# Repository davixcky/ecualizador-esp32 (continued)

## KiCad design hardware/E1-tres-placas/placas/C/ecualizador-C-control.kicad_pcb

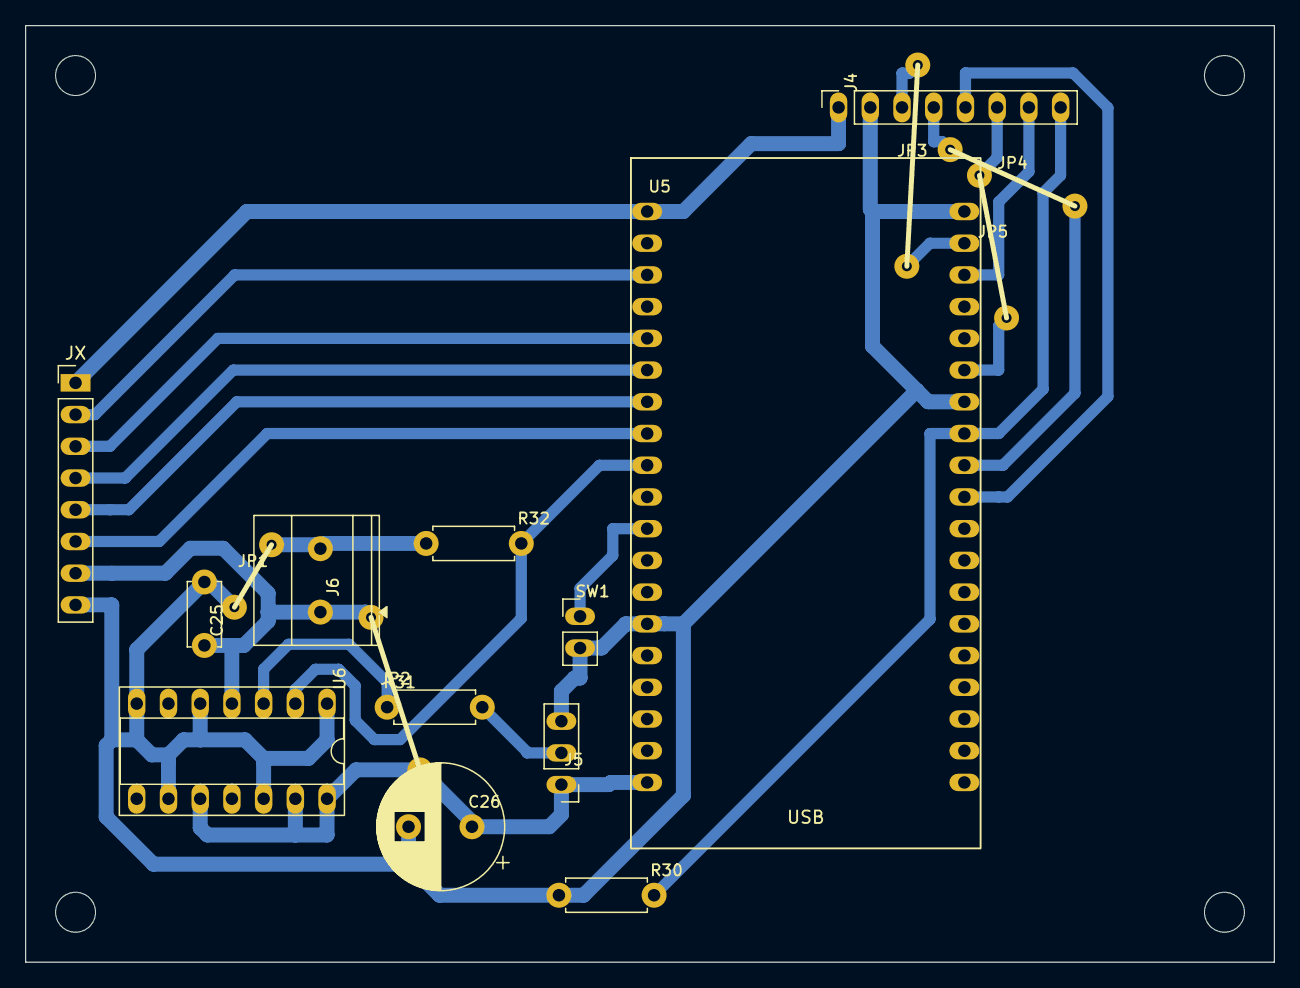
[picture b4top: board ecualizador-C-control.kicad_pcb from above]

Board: 2 copper layers, 100.0 x 75.0 mm, 21 parts (0 on the bottom side), 18 nets.

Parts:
C25: 100n; UnaCara_C25
C26: 1000u 10V; UnaCara_C26
H1, H2, H3, H4: MountingHole_3.2mm_M3
J4: Waveshare 1.9 ST7789V2; UnaCara_J4
J5: NeoPixel 5V DIN GND; UnaCara_J5
J6: Entrada 5V 3A; UnaCara_J6
JP1, JP2, JP3, JP4, JP5: puente; Puente_alambre
JX: Conector entre placas; PinHeader_1x08_P2.54mm_Vertical
R30: 10k; UnaCara_R30
R31: 330; UnaCara_R31
R32: 10k; UnaCara_R32
SW1: Pulsador; UnaCara_SW1
U5: ESP32-DevKitC V4; UnaCara_U5
U6: 74AHCT125; UnaCara_U6

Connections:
+3V3: J4.1, JX.1, U5.1
+5V: C25.1, C26.1, J5.1, J6.1, JP2.1, JX.7, U5.19, U6.4, U6.10, U6.13, U6.14
/ADC_A: JX.5, U5.7
/ADC_FFT: JX.6, U5.8
/ADC_G: JX.3, U5.5
/ADC_M: JX.4, U5.6
/BTN: SW1.1, U5.11
/LED_5V: R31.1, U6.3
/LED_DATA: R32.1, U5.9, U6.2
/LED_DIN: J5.2, R31.2
/TFT_BL: J4.8, R30.1, U5.27
/TFT_CS: J4.5, U5.29
/TFT_DC: J4.6, JP5.1, U5.25
/TFT_MOSI: J4.3, JP3.1, U5.21
/TFT_RST: J4.7, U5.22
/TFT_SCK: J4.4, JP4.1, U5.28
/VREF: JX.2, U5.3
GND: C25.2, C26.2, J4.2, J5.3, J6.2, JP1.1, JX.8, R30.2, R32.2, SW1.2, U5.14, U5.20, U5.26, U6.1, U6.5, U6.7, U6.9, U6.12

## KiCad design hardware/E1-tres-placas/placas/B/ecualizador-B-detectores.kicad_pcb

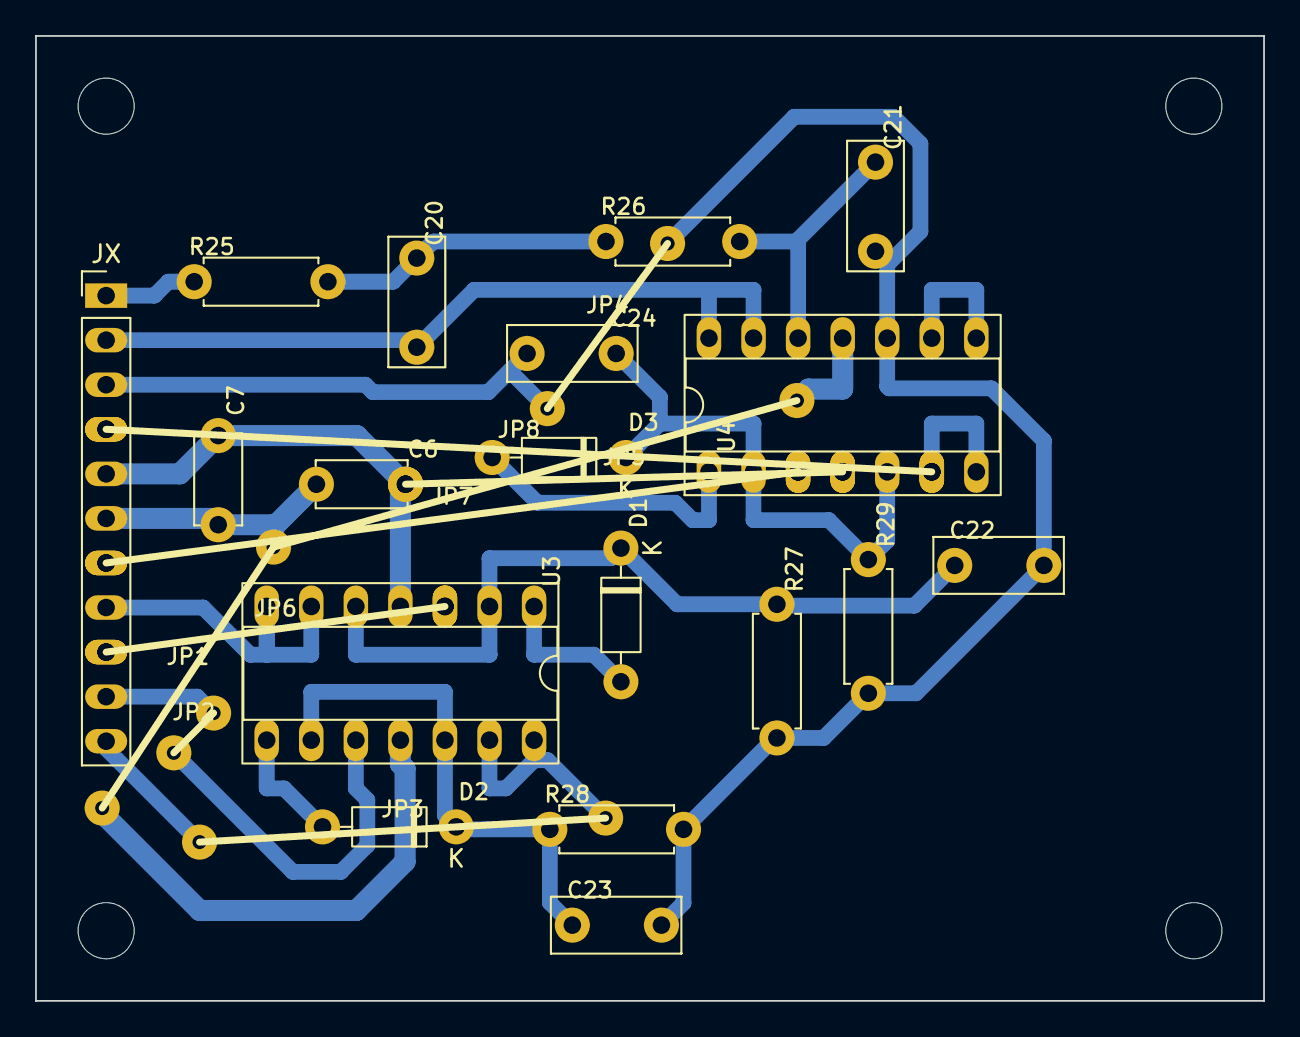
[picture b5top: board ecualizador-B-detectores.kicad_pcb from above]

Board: 2 copper layers, 70.0 x 55.0 mm, 30 parts (0 on the bottom side), 20 nets.

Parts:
C6: 100n; UnaCara_C6
C7: 100n; UnaCara_C7
C20: 4n7 film; UnaCara_C20
C21: 2n2 film; UnaCara_C21
C22: 100n film; UnaCara_C22
C23: 100n film; UnaCara_C23
C24: 100n film; UnaCara_C24
D1: 1N4148; UnaCara_D1
D2: 1N4148; UnaCara_D2
D3: 1N4148; UnaCara_D3
H1, H2, H3, H4: MountingHole_3.2mm_M3
JP1, JP2, JP3, JP4, JP5, JP6, JP7, JP8: puente; Puente_alambre
JX: Conector entre placas; PinHeader_1x11_P2.54mm_Vertical
R25: 10k 1%; UnaCara_R25
R26: 10k 1%; UnaCara_R26
R27: 220k; UnaCara_R27
R28: 220k; UnaCara_R28
R29: 220k; UnaCara_R29
U3: MCP6004; UnaCara_U3
U4: MCP6004; UnaCara_U4

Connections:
+3.3VA: C6.1, C7.1, JP5.1, JX.5, U3.4, U4.4
/ADC_A: JP8.1, JX.4, U4.6, U4.7
/ADC_FFT: C20.2, JX.2, U4.13, U4.14
/ADC_G: JX.8, U3.6, U3.7
/ADC_M: JP3.1, JX.11, U3.13, U3.14
/A_W: JP7.1, JX.7, U4.3
/EQ_OUT: JX.1, R25.1
/G_W: JP6.1, JX.9, U3.3
/M_W: JP2.1, JX.10, U3.10
/VREF: C21.2, C22.2, C23.2, C24.2, JP4.1, JX.3, R27.2, R28.2, R29.2, U4.10
GND: C6.2, C7.2, JP1.1, JX.6, U3.11, U4.11
unnamed: C20.1, R25.2, R26.1
unnamed: D1.2, U3.1
unnamed: C22.1, D1.1, R27.1, U3.2, U3.5
unnamed: D2.2, U3.8
unnamed: C23.1, D2.1, R28.1, U3.9, U3.12
unnamed: D3.2, U4.1
unnamed: C24.1, D3.1, R29.1, U4.2, U4.5
unnamed: C21.1, R26.2, U4.12
unnamed: U4.8, U4.9

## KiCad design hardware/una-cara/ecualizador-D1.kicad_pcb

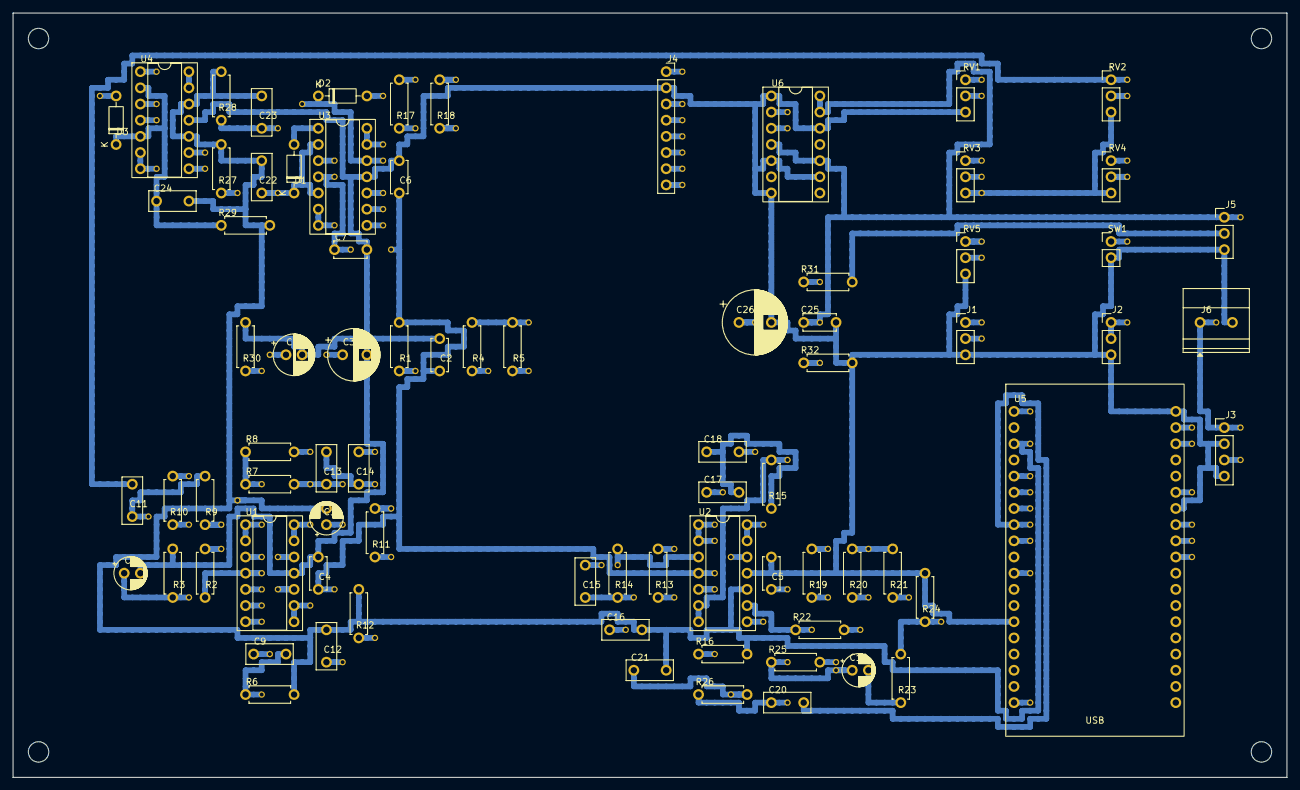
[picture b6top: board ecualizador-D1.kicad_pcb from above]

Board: 2 copper layers, 200.0 x 120.0 mm, 163 parts (0 on the bottom side), 59 nets.

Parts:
C1: 100u 10V; UnaCara_C1
C2: 100n; UnaCara_C2
C3: 470u 10V; UnaCara_C3
C4: 100n; UnaCara_C4
C5: 100n; UnaCara_C5
C6: 100n; UnaCara_C6
C7: 100n; UnaCara_C7
C8: 10u 16V; UnaCara_C8
C9: 1u film; UnaCara_C9
C10: 10u 16V; UnaCara_C10
C11: 100n film; UnaCara_C11
C12: 47n film; UnaCara_C12
C13: 10n film; UnaCara_C13
C14: 10n film; UnaCara_C14
C15: 10n film; UnaCara_C15
C16: 4n7 film; UnaCara_C16
C17: 10n film; UnaCara_C17
C18: 10n film; UnaCara_C18
C19: 10u 16V; UnaCara_C19
C20: 4n7 film; UnaCara_C20
C21: 2n2 film; UnaCara_C21
C22: 100n film; UnaCara_C22
C23: 100n film; UnaCara_C23
C24: 100n film; UnaCara_C24
C25: 100n; UnaCara_C25
C26: 1000u 10V; UnaCara_C26
D1: 1N4148; UnaCara_D1
D2: 1N4148; UnaCara_D2
D3: 1N4148; UnaCara_D3
H1, H2, H3, H4: MountingHole_3.2mm_M3
J1: Entrada de línea 3,5 mm; UnaCara_J1
J2: Salida de línea 3,5 mm; UnaCara_J2
J3: PAM8403; UnaCara_J3
J4: Waveshare 1.9 ST7789V2; UnaCara_J4
J5: NeoPixel 5V DIN GND; UnaCara_J5
J6: Entrada 5V 3A; UnaCara_J6
R1: 10; UnaCara_R1
R2: 10k 1%; UnaCara_R2
R3: 10k 1%; UnaCara_R3
R4: 10k; UnaCara_R4
R5: 10k; UnaCara_R5
R6: 100k; UnaCara_R6
R7: 22k 1%; UnaCara_R7
R8: 10k 1%; UnaCara_R8
R9: 10k 1%; UnaCara_R9
R10: 10k 1%; UnaCara_R10
R11: 27k 1%; UnaCara_R11
R12: 56k 1%; UnaCara_R12
R13: 10k 1%; UnaCara_R13
R14: 10k 1%; UnaCara_R14
R15: 2k7 1%; UnaCara_R15
R16: 5k6 1%; UnaCara_R16
R17: 47k 1%; UnaCara_R17
R18: 47k 1%; UnaCara_R18
R19: 47k 1%; UnaCara_R19
R20: 47k 1%; UnaCara_R20
R21: 47k 1%; UnaCara_R21
R22: 100k 1%; UnaCara_R22
R23: 100; UnaCara_R23
R24: 47k; UnaCara_R24
R25: 10k 1%; UnaCara_R25
R26: 10k 1%; UnaCara_R26
R27: 220k; UnaCara_R27
R28: 220k; UnaCara_R28
R29: 220k; UnaCara_R29
R30: 10k; UnaCara_R30
R31: 330; UnaCara_R31
R32: 10k; UnaCara_R32
RV1: 10k log; UnaCara_RV1
RV2: 10k lin; UnaCara_RV2
RV3: 10k lin; UnaCara_RV3
RV4: 10k lin; UnaCara_RV4
RV5: 10k log; UnaCara_RV5
SW1: Pulsador; UnaCara_SW1
U1: MCP6004; UnaCara_U1
U2: MCP6004; UnaCara_U2
U3: MCP6004; UnaCara_U3
U4: MCP6004; UnaCara_U4
U5: ESP32-DevKitC V4; UnaCara_U5
U6: 74AHCT125; UnaCara_U6
W1, W2: Cable aislado /VREF
W3, W4, W5, W6, W7: Cable aislado +3.3VA
W8, W9, W10, W11: Cable aislado +5V
W12, W13: Cable aislado /LINEA
W14, W15, W16: Cable aislado /PRE
W17: Cable aislado Net-(D1-K)
W18, W19: Cable aislado Net-(D2-K)
W20, W21: Cable aislado Net-(U2C--)
W22: Cable aislado /ADC_FFT
W23: Cable aislado /AGUDOS
W24, W25: Cable aislado /EQ_OUT
W26: Cable aislado /GRAVES
W27, W28: Cable aislado /MEDIOS
W29, W30: Cable aislado /MED_HP
W31, W32: Cable aislado Net-(U1A-+)
W33, W34: Cable aislado +3V3
W35: Cable aislado /ADC_A
W36: Cable aislado /ADC_G
W37: Cable aislado /ADC_M
W38, W39: Cable aislado /A_W
W40, W41: Cable aislado /G_W
W42, W43: Cable aislado /LED_DATA
W44, W45: Cable aislado /M_INV
W46, W47: Cable aislado /M_W
W48, W49: Cable aislado /TFT_BL
W50: Cable aislado Net-(C11-Pad1)
W51: Cable aislado Net-(C13-Pad2)
W52: Cable aislado Net-(C15-Pad1)
W53: Cable aislado Net-(C20-Pad1)
W54: Cable aislado Net-(R4-Pad2)
W55: Cable aislado Net-(U1B-+)
W56: Cable aislado Net-(U1B--)
W57, W58: Cable aislado Net-(U1C-+)
W59, W60: Cable aislado Net-(U1D-+)
W61: Cable aislado Net-(U2A-+)
W62, W63: Cable aislado Net-(U2B-+)
W64: Cable aislado Net-(U2D-+)
W65, W66: Cable aislado Net-(U4C--)
W67: Cable aislado /AMP_IN
W68: Cable aislado /BTN
W69: Cable aislado /IN_L
W70: Cable aislado /IN_R
W71: Cable aislado /LED_5V
W72: Cable aislado /TFT_CS
W73: Cable aislado /TFT_DC
W74: Cable aislado /TFT_MOSI
W75: Cable aislado /TFT_RST
W76: Cable aislado /TFT_SCK
W77: Cable aislado Net-(C10-Pad1)
W78: Cable aislado Net-(C9-Pad1)
W79: Cable aislado Net-(D2-A)
W80: Cable aislado Net-(D3-A)

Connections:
+3.3VA: C1.1, C2.1, C4.1, C5.1, C6.1, C7.1, R1.2, R2.1, U1.4, U2.4, U3.4, U4.4, W3.1, W3.2, W4.1, W4.2, W5.1, W5.2, W6.1, W6.2, W7.1, W7.2
+3V3: J4.1, R1.1, U5.1, W33.1, W33.2, W34.1, W34.2
+5V: C3.1, C25.1, C26.1, J3.1, J5.1, J6.1, U5.19, U6.4, U6.10, U6.13, U6.14, W8.1, W8.2, W9.1, W9.2, W10.1, W10.2, W11.1, W11.2
/ADC_A: U4.6, U4.7, U5.7, W35.1, W35.2
/ADC_FFT: C20.2, U2.13, U2.14, U5.8, W22.1, W22.2
/ADC_G: U3.6, U3.7, U5.5, W36.1, W36.2
/ADC_M: U3.13, U3.14, U5.6, W37.1, W37.2
/AGUDOS: R15.2, RV4.1, U2.6, U2.7, W23.1, W23.2
/AMP_IN: J3.3, RV5.2, W67.1, W67.2
/A_W: R21.1, RV4.2, U4.3, W38.1, W38.2, W39.1, W39.2
/BTN: SW1.1, U5.11, W68.1, W68.2
/EQ_OUT: C19.1, R22.2, R25.1, U2.8, W24.1, W24.2, W25.1, W25.2
/GRAVES: C11.2, RV2.1, U1.8, U1.9, W26.1, W26.2
/G_W: R19.1, RV2.2, U3.3, W40.1, W40.2, W41.1, W41.2
/IN_L: J1.T, R4.1, W69.1, W69.2
/IN_R: J1.R, R5.1, W70.1, W70.2
/LED_5V: R31.1, U6.3, W71.1, W71.2
/LED_DATA: R32.1, U5.9, U6.2, W42.1, W42.2, W43.1, W43.2
/LED_DIN: J5.2, R31.2
/LINEA: J2.R, J2.T, R23.2, R24.1, RV5.1, W12.1, W12.2, W13.1, W13.2
/MEDIOS: C15.2, RV3.1, U2.1, U2.2, W27.1, W27.2, W28.1, W28.2
/MED_HP: R11.2, R13.1, U1.13, U1.14, W29.1, W29.2, W30.1, W30.2
/M_INV: R18.2, R20.1, U4.8, W44.1, W44.2, W45.1, W45.2
/M_W: R17.1, RV3.2, U3.10, W46.1, W46.2, W47.1, W47.2
/PRE: C13.1, C17.1, R7.2, R9.1, U1.7, W14.1, W14.2, W15.1, W15.2, W16.1, W16.2
/TFT_BL: J4.8, R30.1, U5.27, W48.1, W48.2, W49.1, W49.2
/TFT_CS: J4.5, U5.29, W72.1, W72.2
/TFT_DC: J4.6, U5.25, W73.1, W73.2
/TFT_MOSI: J4.3, U5.21, W74.1, W74.2
/TFT_RST: J4.7, U5.22, W75.1, W75.2
/TFT_SCK: J4.4, U5.28, W76.1, W76.2
/VREF: C10.2, C12.2, C16.2, C21.2, C22.2, C23.2, C24.2, R6.2, R12.2, R16.2, R27.2, R28.2, R29.2, RV2.3, RV3.3, RV4.3, U1.1, U1.2, U2.10, U4.10, U4.12, U5.3, W1.1, W1.2, W2.1, W2.2
GND: C1.2, C2.2, C3.2, C4.2, C5.2, C6.2, C7.2, C8.2, C25.2, C26.2, J1.S, J2.S, J3.2, J3.4, J4.2, J5.3, J6.2, R3.2, R24.2, R30.2, R32.2, RV1.3, RV5.3, SW1.2, U1.11, U2.11, U3.11, U4.11, U5.14, U5.20, U5.26, U6.1, U6.5, U6.7, U6.9, U6.12
unnamed: C9.1, RV1.2, W78.1, W78.2
unnamed: C10.1, R8.2, W77.1, W77.2
unnamed: C11.1, R9.2, R10.1, W50.1, W50.2
unnamed: C13.2, C14.1, R11.1, W51.1, W51.2
unnamed: C15.1, R13.2, R14.1, W52.1, W52.2
unnamed: C17.2, C18.1, R15.1
unnamed: C19.2, R23.1
unnamed: C20.1, R25.2, R26.1, W53.1, W53.2
unnamed: D1.2, U3.1
unnamed: C22.1, D1.1, R27.1, U3.2, U3.5, W17.1, W17.2
unnamed: D2.2, U3.8, W79.1, W79.2
unnamed: C23.1, D2.1, R28.1, U3.9, U3.12, W18.1, W18.2, W19.1, W19.2
unnamed: D3.2, U4.1, W80.1, W80.2
unnamed: C24.1, D3.1, R29.1, U4.2, U4.5
unnamed: R4.2, R5.2, RV1.1, W54.1, W54.2
unnamed: C8.1, R2.2, R3.1, U1.3, W31.1, W31.2, W32.1, W32.2
unnamed: C9.2, R6.1, U1.5, W55.1, W55.2
unnamed: R7.1, R8.1, U1.6, W56.1, W56.2
unnamed: C12.1, R10.2, U1.10, W57.1, W57.2, W58.1, W58.2
unnamed: C14.2, R12.1, U1.12, W59.1, W59.2, W60.1, W60.2
unnamed: C16.1, R14.2, U2.3, W61.1, W61.2
unnamed: C18.2, R16.1, U2.5, W62.1, W62.2, W63.1, W63.2
unnamed: R19.2, R20.2, R21.2, R22.1, U2.9, W20.1, W20.2, W21.1, W21.2
unnamed: C21.1, R26.2, U2.12, W64.1, W64.2
unnamed: R17.2, R18.1, U4.9, W65.1, W65.2, W66.1, W66.2
unnamed: U4.13, U4.14

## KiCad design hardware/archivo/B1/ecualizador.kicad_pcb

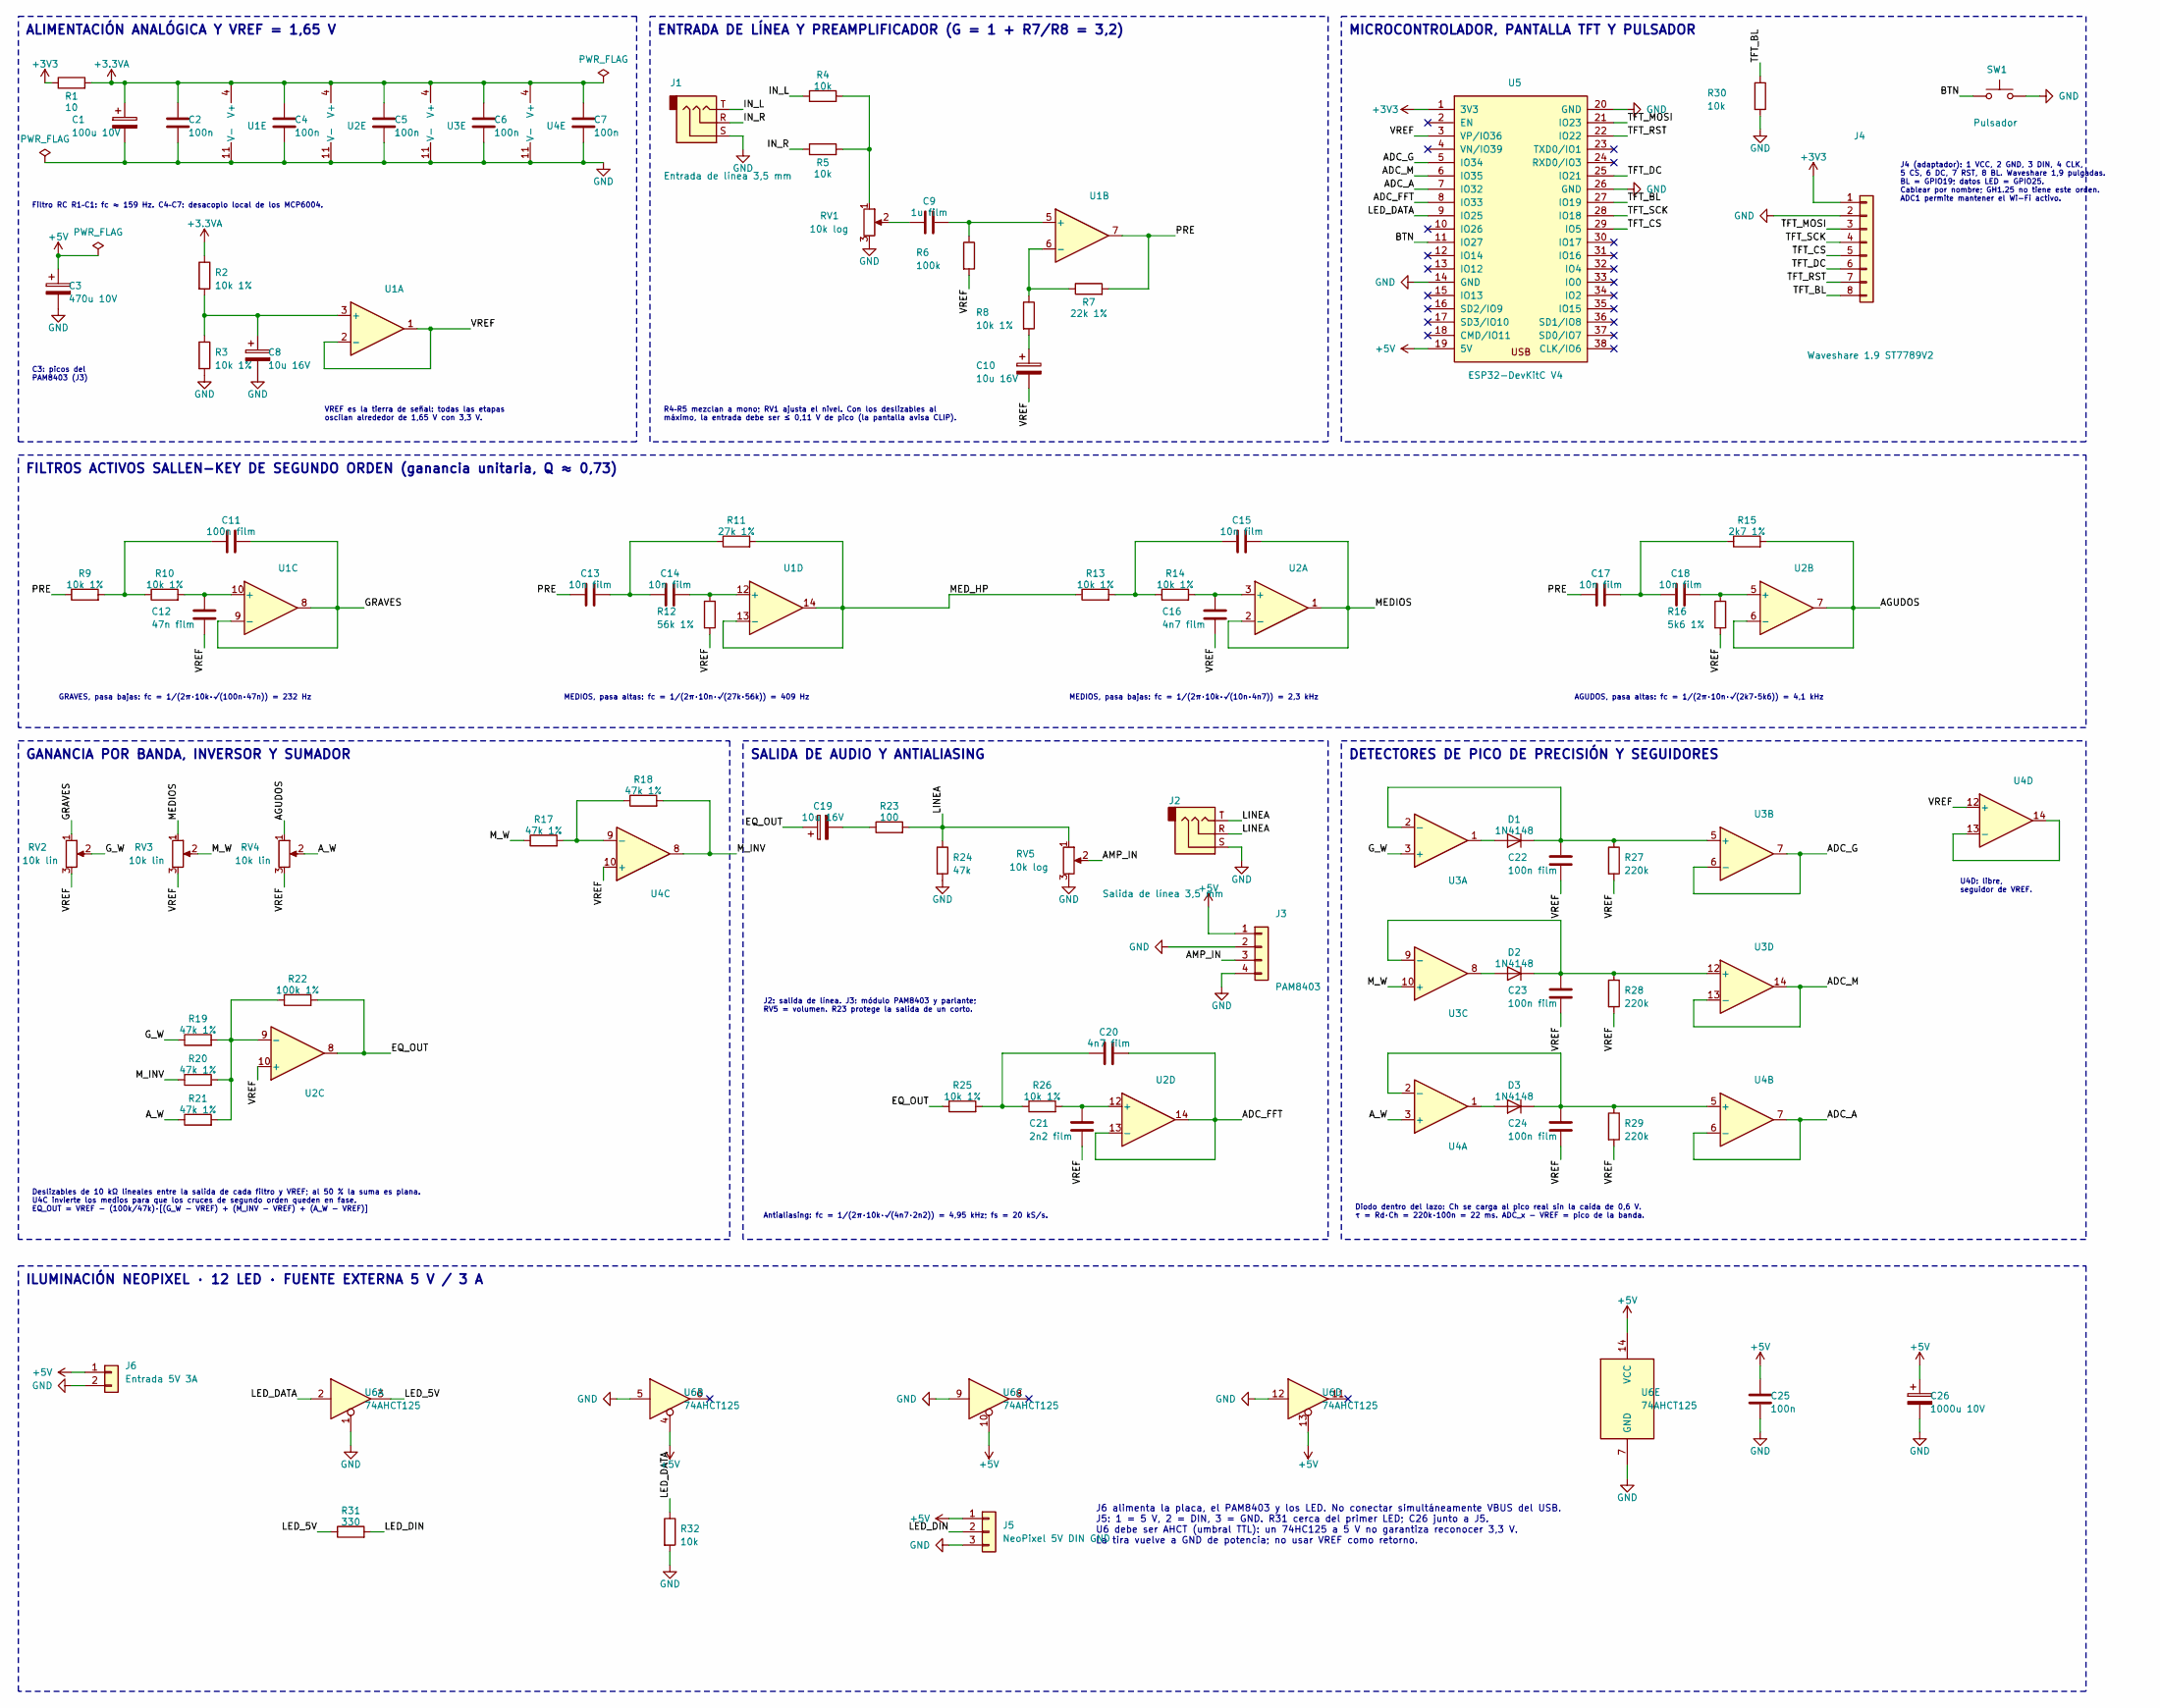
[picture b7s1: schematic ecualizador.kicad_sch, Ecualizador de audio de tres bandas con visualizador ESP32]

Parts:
C1: 100u 10V; UnaCara_C1
C2: 100n; UnaCara_C2
C3: 470u 10V; UnaCara_C3
C4: 100n; UnaCara_C4
C5: 100n; UnaCara_C5
C6: 100n; UnaCara_C6
C7: 100n; UnaCara_C7
C8: 10u 16V; UnaCara_C8
C9: 1u film; UnaCara_C9
C10: 10u 16V; UnaCara_C10
C11: 100n film; UnaCara_C11
C12: 47n film; UnaCara_C12
C13: 10n film; UnaCara_C13
C14: 10n film; UnaCara_C14
C15: 10n film; UnaCara_C15
C16: 4n7 film; UnaCara_C16
C17: 10n film; UnaCara_C17
C18: 10n film; UnaCara_C18
C19: 10u 16V; UnaCara_C19
C20: 4n7 film; UnaCara_C20
C21: 2n2 film; UnaCara_C21
C22: 100n film; UnaCara_C22
C23: 100n film; UnaCara_C23
C24: 100n film; UnaCara_C24
C25: 100n; UnaCara_C25
C26: 1000u 10V; UnaCara_C26
D1: 1N4148; UnaCara_D1
D2: 1N4148; UnaCara_D2
D3: 1N4148; UnaCara_D3
J1: Entrada de línea 3,5 mm; UnaCara_J1
J2: Salida de línea 3,5 mm; UnaCara_J2
J3: PAM8403; UnaCara_J3
J4: Waveshare 1.9 ST7789V2; UnaCara_J4
J5: NeoPixel 5V DIN GND; UnaCara_J5
J6: Entrada 5V 3A; UnaCara_J6
R1: 10; UnaCara_R1
R2: 10k 1%; UnaCara_R2
R3: 10k 1%; UnaCara_R3
R4: 10k; UnaCara_R4
R5: 10k; UnaCara_R5
R6: 100k; UnaCara_R6
R7: 22k 1%; UnaCara_R7
R8: 10k 1%; UnaCara_R8
R9: 10k 1%; UnaCara_R9
R10: 10k 1%; UnaCara_R10
R11: 27k 1%; UnaCara_R11
R12: 56k 1%; UnaCara_R12
R13: 10k 1%; UnaCara_R13
R14: 10k 1%; UnaCara_R14
R15: 2k7 1%; UnaCara_R15
R16: 5k6 1%; UnaCara_R16
R17: 47k 1%; UnaCara_R17
R18: 47k 1%; UnaCara_R18
R19: 47k 1%; UnaCara_R19
R20: 47k 1%; UnaCara_R20
R21: 47k 1%; UnaCara_R21
R22: 100k 1%; UnaCara_R22
R23: 100; UnaCara_R23
R24: 47k; UnaCara_R24
R25: 10k 1%; UnaCara_R25
R26: 10k 1%; UnaCara_R26
R27: 220k; UnaCara_R27
R28: 220k; UnaCara_R28
R29: 220k; UnaCara_R29
R30: 10k; UnaCara_R30
R31: 330; UnaCara_R31
R32: 10k; UnaCara_R32
RV1: 10k log; UnaCara_RV1
RV2: 10k lin; UnaCara_RV2
RV3: 10k lin; UnaCara_RV3
RV4: 10k lin; UnaCara_RV4
RV5: 10k log; UnaCara_RV5
SW1: Pulsador; UnaCara_SW1
U1: MCP6004; UnaCara_U1
U2: MCP6004; UnaCara_U2
U3: MCP6004; UnaCara_U3
U4: MCP6004; UnaCara_U4
U5: ESP32-DevKitC V4; UnaCara_U5
U6: 74AHCT125; UnaCara_U6

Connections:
+3.3VA: C1.1, C2.1, C4.1, C5.1, C6.1, C7.1, R1.2, R2.1, U1.4 (V+), U2.4 (V+), U3.4 (V+), U4.4 (V+)
+3V3: J4.1, R1.1, U5.1 (3V3)
+5V: C3.1, C25.1, C26.1, J3.1, J5.1, J6.1, U5.19 (5V), U6.4, U6.10, U6.13, U6.14 (VCC)
/ADC_A: U4.6 (-), U4.7, U5.7 (IO32)
/ADC_FFT: C20.2, U2.13 (-), U2.14, U5.8 (IO33)
/ADC_G: U3.6 (-), U3.7, U5.5 (IO34)
/ADC_M: U3.13 (-), U3.14, U5.6 (IO35)
/AGUDOS: R15.2, RV4.1, U2.6 (-), U2.7
/AMP_IN: J3.3, RV5.2
/A_W: R21.1, RV4.2, U4.3 (+)
/BTN: SW1.1, U5.11 (IO27)
/EQ_OUT: C19.1, R22.2, R25.1, U2.8
/GRAVES: C11.2, RV2.1, U1.8, U1.9 (-)
/G_W: R19.1, RV2.2, U3.3 (+)
/IN_L: J1.T, R4.1
/IN_R: J1.R, R5.1
/LED_5V: R31.1, U6.3
/LED_DATA: R32.1, U5.9 (IO25), U6.2
/LED_DIN: J5.2, R31.2
/LINEA: J2.R, J2.T, R23.2, R24.1, RV5.1
/MEDIOS: C15.2, RV3.1, U2.1, U2.2 (-)
/MED_HP: R11.2, R13.1, U1.13 (-), U1.14
/M_INV: R18.2, R20.1, U4.8
/M_W: R17.1, RV3.2, U3.10 (+)
/PRE: C13.1, C17.1, R7.2, R9.1, U1.7
/TFT_BL: J4.8, R30.1, U5.27 (IO19)
/TFT_CS: J4.5, U5.29 (IO5)
/TFT_DC: J4.6, U5.25 (IO21)
/TFT_MOSI: J4.3, U5.21 (IO23)
/TFT_RST: J4.7, U5.22 (IO22)
/TFT_SCK: J4.4, U5.28 (IO18)
/VREF: C10.2, C12.2, C16.2, C21.2, C22.2, C23.2, C24.2, R6.2, R12.2, R16.2, R27.2, R28.2, R29.2, RV2.3, RV3.3, RV4.3, U1.1, U1.2 (-), U2.10 (+), U4.10 (+), U4.12 (+), U5.3 (VP/IO36)
GND: C1.2, C2.2, C3.2, C4.2, C5.2, C6.2, C7.2, C8.2, C25.2, C26.2, J1.S, J2.S, J3.2, J3.4, J4.2, J5.3, J6.2, R3.2, R24.2, R30.2, R32.2, RV1.3, RV5.3, SW1.2, U1.11 (V-), U2.11 (V-), U3.11 (V-), U4.11 (V-), U5.14 (GND), U5.20 (GND), U5.26 (GND), U6.1, U6.5, U6.7 (GND), U6.9, U6.12
unnamed: C9.1, RV1.2
unnamed: C10.1, R8.2
unnamed: C11.1, R9.2, R10.1
unnamed: C13.2, C14.1, R11.1
unnamed: C15.1, R13.2, R14.1
unnamed: C17.2, C18.1, R15.1
unnamed: C19.2, R23.1
unnamed: C20.1, R25.2, R26.1
unnamed: D1.2 (A), U3.1
unnamed: C22.1, D1.1 (K), R27.1, U3.2 (-), U3.5 (+)
unnamed: D2.2 (A), U3.8
unnamed: C23.1, D2.1 (K), R28.1, U3.9 (-), U3.12 (+)
unnamed: D3.2 (A), U4.1
unnamed: C24.1, D3.1 (K), R29.1, U4.2 (-), U4.5 (+)
unnamed: R4.2, R5.2, RV1.1
unnamed: C8.1, R2.2, R3.1, U1.3 (+)
unnamed: C9.2, R6.1, U1.5 (+)
unnamed: R7.1, R8.1, U1.6 (-)
unnamed: C12.1, R10.2, U1.10 (+)
unnamed: C14.2, R12.1, U1.12 (+)
unnamed: C16.1, R14.2, U2.3 (+)
unnamed: C18.2, R16.1, U2.5 (+)
unnamed: R19.2, R20.2, R21.2, R22.1, U2.9 (-)
unnamed: C21.1, R26.2, U2.12 (+)
unnamed: R17.2, R18.1, U4.9 (-)
unnamed: U4.13 (-), U4.14

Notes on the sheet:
ALIMENTACIÓN ANALÓGICA Y VREF = 1,65 V
Filtro RC R1–C1: fc ≈ 159 Hz. C4–C7: desacoplo local de los MCP6004.
C3: picos del PAM8403 (J3)
VREF es la tierra de señal: todas las etapas oscilan alrededor de 1,65 V con 3,3 V.
ENTRADA DE LÍNEA Y PREAMPLIFICADOR (G = 1 + R7/R8 = 3,2)
R4–R5 mezclan a mono; RV1 ajusta el nivel. Con los deslizables al máximo, la entrada debe ser ≤ 0,11 V de pico (la pantalla avisa CLIP).
MICROCONTROLADOR, PANTALLA TFT Y PULSADOR
J4 (adaptador): 1 VCC, 2 GND, 3 DIN, 4 CLK, 5 CS, 6 DC, 7 RST, 8 BL. Waveshare 1,9 pulgadas. BL = GPIO19; datos LED = GPIO25. Cablear por nombre; GH1.25 no tiene este orden. ADC1 permite mantener el Wi-Fi activo.
FILTROS ACTIVOS SALLEN-KEY DE SEGUNDO ORDEN (ganancia unitaria, Q ≈ 0,73)
GRAVES, pasa bajas: fc = 1/(2π·10k·√(100n·47n)) = 232 Hz
MEDIOS, pasa altas: fc = 1/(2π·10n·√(27k·56k)) = 409 Hz
MEDIOS, pasa bajas: fc = 1/(2π·10k·√(10n·4n7)) = 2,3 kHz
AGUDOS, pasa altas: fc = 1/(2π·10n·√(2k7·5k6)) = 4,1 kHz
GANANCIA POR BANDA, INVERSOR Y SUMADOR
Deslizables de 10 kΩ lineales entre la salida de cada filtro y VREF; al 50 % la suma es plana. U4C invierte los medios para que los cruces de segundo orden queden en fase. EQ_OUT = VREF − (100k/47k)·[(G_W − VREF) + (M_INV − VREF) + (A_W − VREF)]
SALIDA DE AUDIO Y ANTIALIASING
J2: salida de línea. J3: módulo PAM8403 y parlante; RV5 = volumen. R23 protege la salida de un corto.
Antialiasing: fc = 1/(2π·10k·√(4n7·2n2)) = 4,95 kHz; fs = 20 kS/s.
DETECTORES DE PICO DE PRECISIÓN Y SEGUIDORES
U4D: libre, seguidor de VREF.
Diodo dentro del lazo: Ch se carga al pico real sin la caída de 0,6 V. τ = Rd·Ch = 220k·100n = 22 ms. ADC_x − VREF = pico de la banda.
ILUMINACIÓN NEOPIXEL · 12 LED · FUENTE EXTERNA 5 V / 3 A
J6 alimenta la placa, el PAM8403 y los LED. No conectar simultáneamente VBUS del USB. J5: 1 = 5 V, 2 = DIN, 3 = GND. R31 cerca del primer LED; C26 junto a J5. U6 debe ser AHCT (umbral TTL): un 74HC125 a 5 V no garantiza reconocer 3,3 V. La tira vuelve a GND de potencia; no usar VREF como retorno.

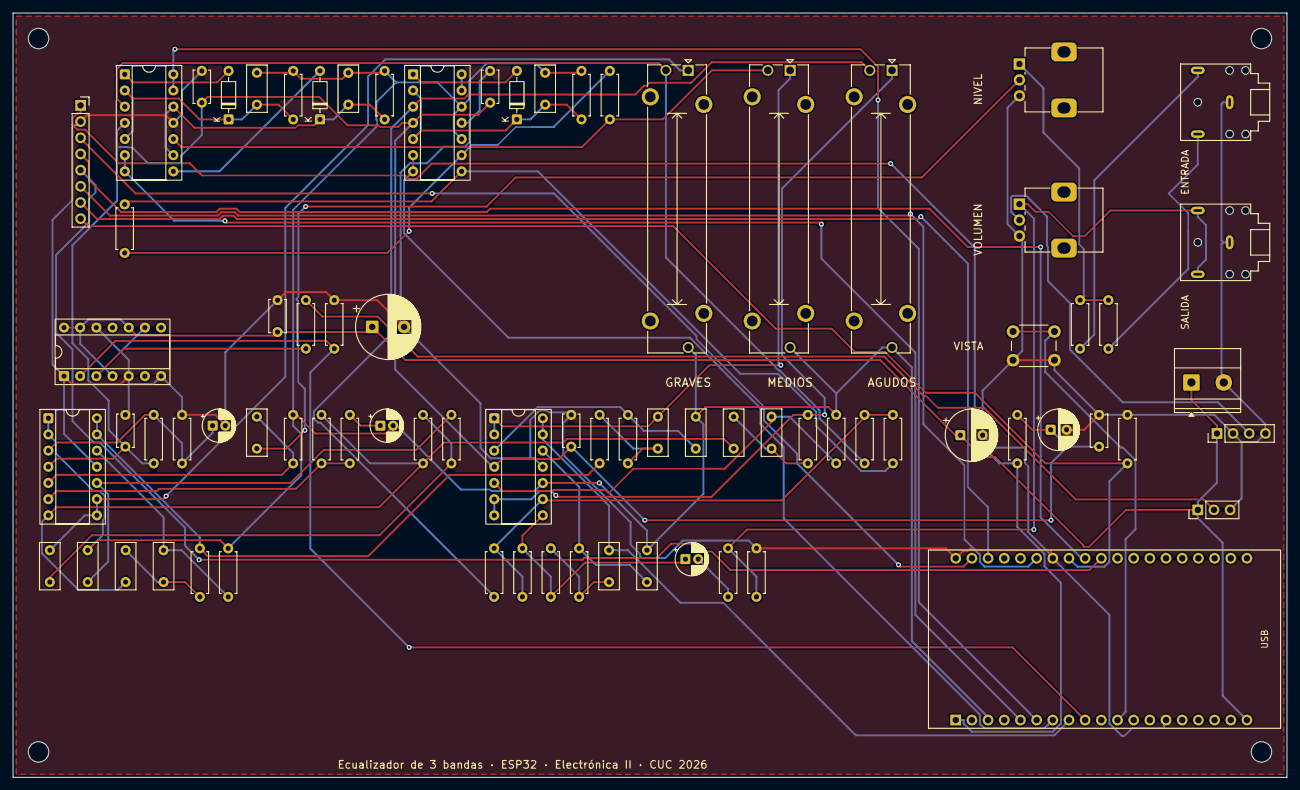
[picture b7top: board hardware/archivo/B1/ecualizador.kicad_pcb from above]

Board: 2 copper layers, 200.0 x 120.0 mm, 83 parts (0 on the bottom side), 59 nets.

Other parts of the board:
H1, H2, H3, H4: MountingHole_3.2mm_M3

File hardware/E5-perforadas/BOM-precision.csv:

categoria,valor,cantidad,referencias,especificacion
Resistencia,10 ohm,1,R1,"pelicula metalica 1% 0.25W"
Resistencia,100 ohm,1,R23,"pelicula metalica 1% 0.25W"
Resistencia,330 ohm,1,R31,"pelicula metalica 1% 0.25W"
Resistencia,2.7 kohm,1,R15,"pelicula metalica 1% 0.25W"
Resistencia,5.6 kohm,1,R16,"pelicula metalica 1% 0.25W"
Resistencia,10 kohm,10,"R2 R3 R33-R40","0.1% recomendado 25ppm/C; parejas criticas"
Resistencia,10 kohm,11,"R4 R5 R8-R10 R13 R14 R25 R26 R30 R32","pelicula metalica 1% 0.25W"
Resistencia,22 kohm,1,R7,"pelicula metalica 1% 0.25W"
Resistencia,27 kohm,1,R11,"pelicula metalica 1% 0.25W"
Resistencia,47 kohm,6,"R17-R21 R24","pelicula metalica 1% 0.25W"
Resistencia,56 kohm,1,R12,"pelicula metalica 1% 0.25W"
Resistencia,100 kohm,2,"R6 R22","pelicula metalica 1% 0.25W"
Resistencia,220 kohm,3,R27-R29,"pelicula metalica 1% mismo lote"
Capacitor pelicula,2.2 nF,1,C21,"pelicula 5% 50V"
Capacitor pelicula,4.7 nF,2,"C16 C20","pelicula 5% 50V mismo lote"
Capacitor pelicula,10 nF,5,"C13-C15 C17 C18","pelicula 5% 50V mismo lote"
Capacitor pelicula,47 nF,1,C12,"pelicula 5% 50V"
Capacitor pelicula,100 nF,4,"C11 C22-C24","pelicula 5% 50V"
Capacitor pelicula,1 uF,1,C9,"pelicula 5% preferido 10% maximo"
Capacitor ceramico,100 nF,6,"C2 C4-C7 C25","X7R 10% 50V"
Capacitor electrolitico,10 uF,2,"C8 C19","polar 16V 105C"
Capacitor bipolar,10 uF,1,C10,"bipolar/no polar 16V o pelicula"
Capacitor electrolitico,100 uF,1,C1,"10V o 16V 105C"
Capacitor electrolitico,470 uF,1,C3,"10V o 16V 105C baja ESR"
Capacitor electrolitico,1000 uF,1,C26,"10V o 16V 105C baja ESR"
Semiconductor,LM324N DIP-14,4,U1-U4,"fabricante reconocido; usar zocalo"
Semiconductor,74HCT245 DIP-20,1,U6,"sustitucion local para NeoPixel; +5V; DIR=1; /OE=0; A0 a B0"
Semiconductor,ESP32-DevKitC V4 38 pines,1,U5,"montar en dos zocalos 1x19"
Diodo,1N4148,3,D1-D3,"mismo lote recomendado"
Potenciometro,10 kohm lineal,3,RV2-RV4,"misma serie y lote"
Potenciometro,10 kohm logaritmico,2,RV1 RV5,"audio/log"
Conector,Jack estereo 3.5mm,2,J1 J2,"terminales T R S identificables"
Conector,Bornera 2 vias 5.08mm,1,J6,"corriente nominal 3A o mayor"
Conector,1x4,1,J3,"PAM8403"
Conector,1x3,1,J5,"NeoPixel"
Conector,1x8,1,J4,"pantalla de ocho senales"
Conector,Cable GH1.25 8 vias,1,Pantalla,"conectar por nombre de senal"
Conector,JST-XH 4 vias macho placa,10,JBUS/JAB/JC4,"arneses entre tarjetas"
Conector,JST-XH 4 vias carcasa hembra,10,JBUS/JAB/JC4,"arneses entre tarjetas"
Conector,JST-XH 5 vias macho placa,2,JBC,"arnes entre T2 y T3"
Conector,JST-XH 5 vias carcasa hembra,2,JBC,"arnes entre T2 y T3"
Conector,JST-XH 2 vias macho placa,2,JB4,"arnes entre T2 y T4"
Conector,JST-XH 2 vias carcasa hembra,2,JB4,"arnes entre T2 y T4"
Conector,Terminal crimp JST-XH,70,Arneses,"se utilizan 54; incluye repuestos"
Control,Pulsador normalmente abierto 6x6mm,1,SW1,"momentaneo"
Modulo,Pantalla Waveshare 1.9 ST7789V2,1,Display,"170x320 SPI"
Modulo,PAM8403,1,Audio,"5V 2x3W"
Modulo,Parlante 4 ohm 3W,1,Audio,"40-50mm"
Modulo,Tira WS2812B 5V,12,LED,"dos tramos de aproximadamente 100mm"
Alimentacion,Fuente regulada 5V 3A,1,J6,"con proteccion contra cortocircuito"
Mecanico,Tarjeta perforada 90x70mm,1,T1,"paso 2.54mm pads individuales"
Mecanico,Tarjeta perforada 100x70mm,2,T2 T3,"paso 2.54mm pads individuales"
Mecanico,Tarjeta perforada 100x80mm,1,T4,"paso 2.54mm pads individuales"
Mecanico,Zocalo DIP-14,4,U1-U4,"preferiblemente torneado"
Mecanico,Zocalo DIP-20,1,U6,"preferiblemente torneado"
Mecanico,Zocalo hembra 1x19,2,U5,"ESP32 de 38 pines"
Cable,Alambre cobre estanado 0.8-1.0mm,4 m,Barras locales,"+5V y GND sobre las cuatro tarjetas"
Cable,Cable 22AWG rojo,3 m,Distribucion,"ramas en estrella +5V"
Cable,Cable 22AWG negro,3 m,Distribucion,"ramas en estrella GND"
Cable,Cable 26AWG varios colores,1,juego,"VREF y senales"
Alimentacion,Bloque distribucion 7 vias o mas,2,Estrella,"uno +5V y uno GND; 5A o mayor"
Alimentacion,Portafusible en linea y fusible 3A,1,J6,"comprar un fusible de repuesto"
Alimentacion,Interruptor general 5A DC,1,J6,"antes de los bloques de distribucion"
Mecanico,Separadores M3 con tornillos,16,Cuatro tarjetas,"cuatro por tarjeta"
